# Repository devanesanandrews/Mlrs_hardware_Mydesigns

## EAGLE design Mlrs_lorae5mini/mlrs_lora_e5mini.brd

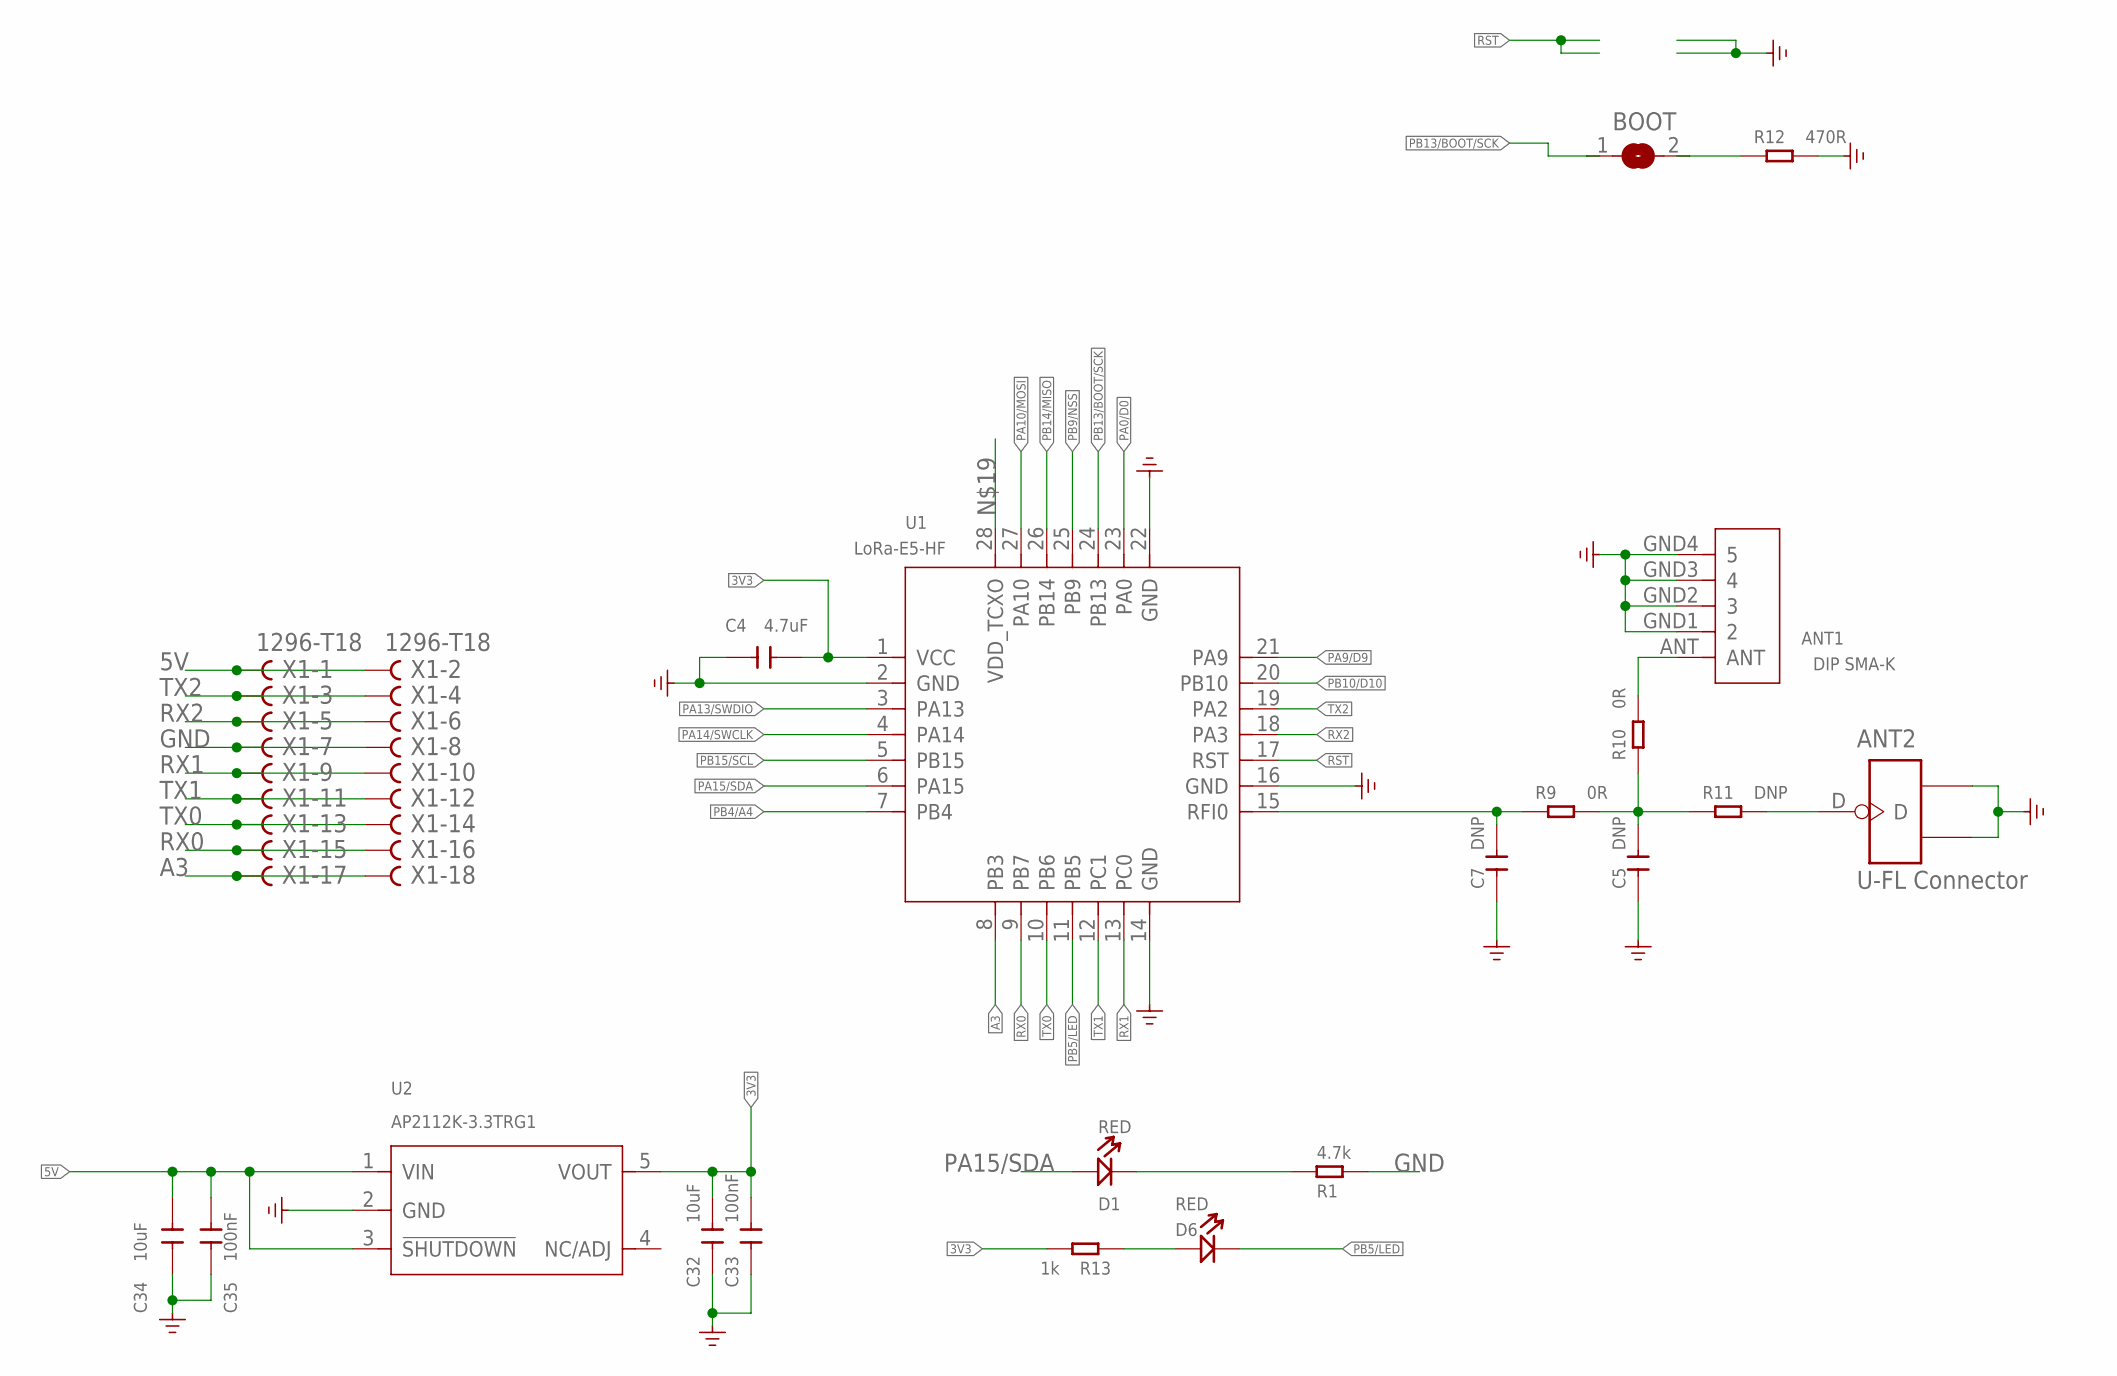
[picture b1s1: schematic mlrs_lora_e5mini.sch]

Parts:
ANT1: DIP SMA-K; SMA5P-SMD-5.1-6.5X6.5X16.5MM
ANT2: U-FL Connector; U-FL3P-SMD-2.6X2.6X1.0MM
BOOT: SJ
C4: 4.7uF; C0603
C5, C7: DNP; C0402
C32, C34: 10uF; C0805
C33, C35: 100nF; C0603
D1, D6: RED; LED-0603
R1: 4.7k; R0402
R9, R10: 0R; R0402
R11: DNP; R0402
R12: 470R; R0402
R13: 1k; R0402
U1: LoRa-E5-HF; MOUDLE28P-1.25-12X12X2.5MM
U2: AP2112K-3.3TRG1; SOT-23-5
X1: 1296-T18; 1296-18

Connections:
3V3: C4.2, C32.2, C33.2, R13.2, U1.1 (VCC), U2.5 (VOUT)
5V: C34.2, C35.2, U2.1 (VIN), U2.3 (!SHUTDOWN), X1.1, X1.2
A3: U1.8 (PB3), X1.17, X1.18
GND: ANT1.GND1 (2), ANT1.GND2 (3), ANT1.GND3 (4), ANT1.GND4 (5), ANT2.GND1, ANT2.GND2, C4.1, C5.1, C7.1, C32.1, C33.1, C34.1, C35.1, R1.2, R12.2, U1.2 (GND), U1.14 (GND), U1.16 (GND), U1.22 (GND), U2.2 (GND), X1.7, X1.8
unnamed: D1.-, R1.1
unnamed: ANT2.D, R11.2
unnamed: D6.+, R13.1
unnamed: ANT1.ANT, R10.2
unnamed: C5.2, R9.2, R10.1, R11.1
unnamed: BOOT.2, R12.1
PA0/D0: U1.23 (PA0)
PA9/D9: U1.21 (PA9)
PA10/MOSI: U1.27 (PA10)
PA13/SWDIO: U1.3 (PA13)
PA14/SWCLK: U1.4 (PA14)
PA15/SDA: D1.+, U1.6 (PA15)
PB4/A4: U1.7 (PB4)
PB5/LED: D6.-, U1.11 (PB5)
PB9/NSS: U1.25 (PB9)
PB10/D10: U1.20 (PB10)
PB13/BOOT/SCK: BOOT.1, U1.24 (PB13)
PB14/MISO: U1.26 (PB14)
PB15/SCL: U1.5 (PB15)
RF: C7.2, R9.1, U1.15 (RFI0)
RST: U1.17 (RST)
RX0: U1.9 (PB7), X1.15, X1.16
RX1: U1.13 (PC0), X1.9, X1.10
RX2: U1.18 (PA3), X1.5, X1.6
TX0: U1.10 (PB6), X1.13, X1.14
TX1: U1.12 (PC1), X1.11, X1.12
TX2: U1.19 (PA2), X1.3, X1.4

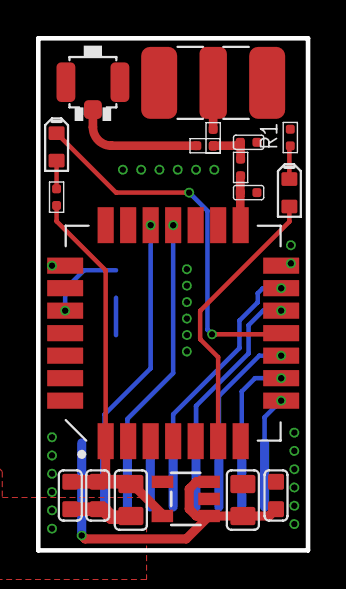
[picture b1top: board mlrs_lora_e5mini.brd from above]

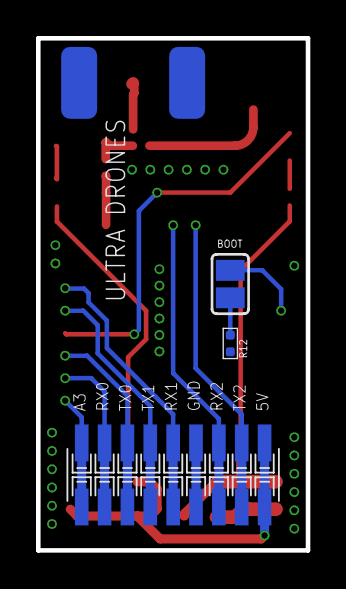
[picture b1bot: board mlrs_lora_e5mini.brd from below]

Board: 2 copper layers, 15.0 x 28.4 mm, 21 parts (3 on the bottom side), 20 nets.
